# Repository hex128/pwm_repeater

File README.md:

# KiCad Project of a simple 12-24V PWM repeater mainly for LED Strips

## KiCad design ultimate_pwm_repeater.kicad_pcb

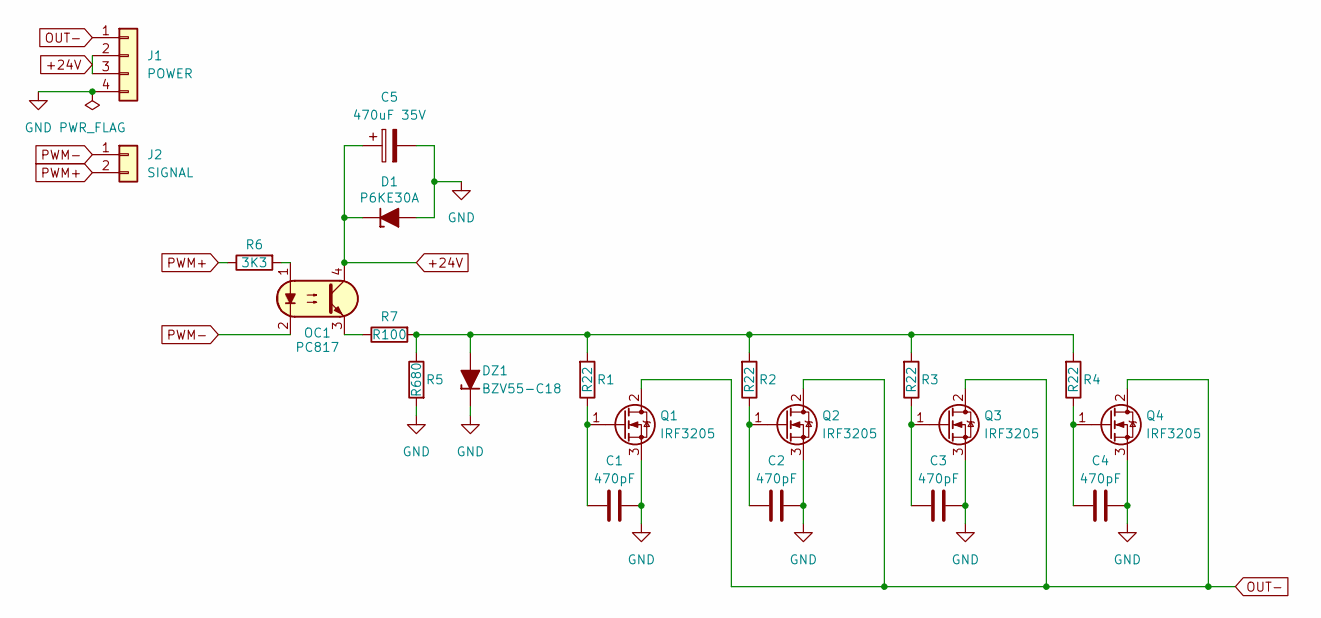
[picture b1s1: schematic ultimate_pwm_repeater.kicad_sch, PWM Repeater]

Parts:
C1, C2, C3, C4: 470pF; C_Disc_D4.7mm_W2.5mm_P5.00mm
C5: 470uF 35V; CP_Radial_D10.0mm_P3.50mm
D1: P6KE30A; D_DO-15_P10.16mm_Horizontal_Zener
DZ1: BZV55-C18; D_MiniMELF
J1: POWER; TerminalBlock_Degson_DG65C-B-04P
J2: SIGNAL; TerminalBlock_Phoenix_MKDS-1,5-2-5.08_1x02_P5.08mm_Horizont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
OC1: PC817; DIP-4_W7.62mm_LongPads
Q1, Q2, Q3, Q4: IRF3205; TO-220-3_Vertical
R1, R2, R3, R4: R22; R_1206_3216Metric; Rating W
R5: R680; R_1206_3216Metric; Rating W
R6: 3K3; R_1206_3216Metric; Rating W
R7: R100; R_1206_3216Metric; Rating W

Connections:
+24V: C5.1, D1.1 (K), J1.2, J1.3, OC1.4
GND: C1.1, C2.2, C3.1, C4.2, C5.2, D1.2 (A), DZ1.1 (K), J1.4, Q1.3 (S), Q2.3 (S), Q3.3 (S), Q4.3 (S), R5.1
unnamed: DZ1.2 (A), R1.1, R2.1, R3.1, R4.1, R5.2, R7.1
unnamed: OC1.1, R6.1
unnamed: OC1.3, R7.2
unnamed: C1.2, Q1.1 (G), R1.2
unnamed: C2.1, Q2.1 (G), R2.2
unnamed: C3.2, Q3.1 (G), R3.2
unnamed: C4.1, Q4.1 (G), R4.2
OUT-: J1.1, Q1.2 (D), Q2.2 (D), Q3.2 (D), Q4.2 (D)
PWM+: J2.2, R6.2
PWM-: J2.1, OC1.2

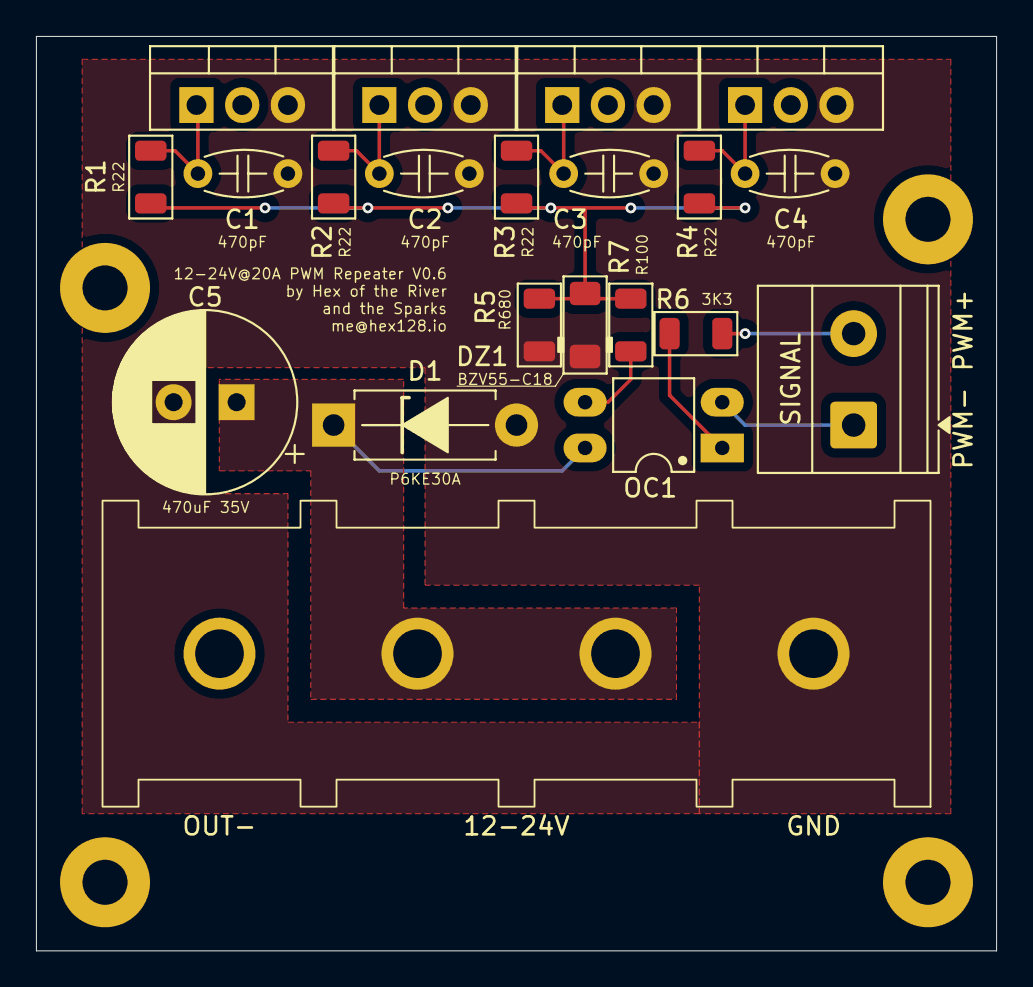
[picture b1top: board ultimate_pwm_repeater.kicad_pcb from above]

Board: 2 copper layers, 53.3 x 50.8 mm, 25 parts (0 on the bottom side), 12 nets.

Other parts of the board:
LH: MountingHole_2.5mm_Pad
LTH: MountingHole_2.5mm_Pad
RH: MountingHole_2.5mm_Pad
RTH: MountingHole_2.5mm_Pad

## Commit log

2025-04-29 init
2025-04-29 images
2025-04-29 readme
2025-04-29 title
2025-04-30 replaced connectors
2025-04-30 updated the revision
2025-04-30 updated the pcb images
2025-04-30 added mounting holes
2025-04-30 re-added the top gnd fill zone (introduced in 0.3)
2025-04-30 updated the version on sch for consistency
2025-05-09 fixed reverse mosfet connection, rearranged pcb
2025-06-10 18v zener, 3.5mm pitch capacitor
2025-06-10 updated images
2025-06-11 updated pcb svg
